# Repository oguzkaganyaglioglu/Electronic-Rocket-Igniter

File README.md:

# Electronic Model Rocket Igniter
## This project still work in progress

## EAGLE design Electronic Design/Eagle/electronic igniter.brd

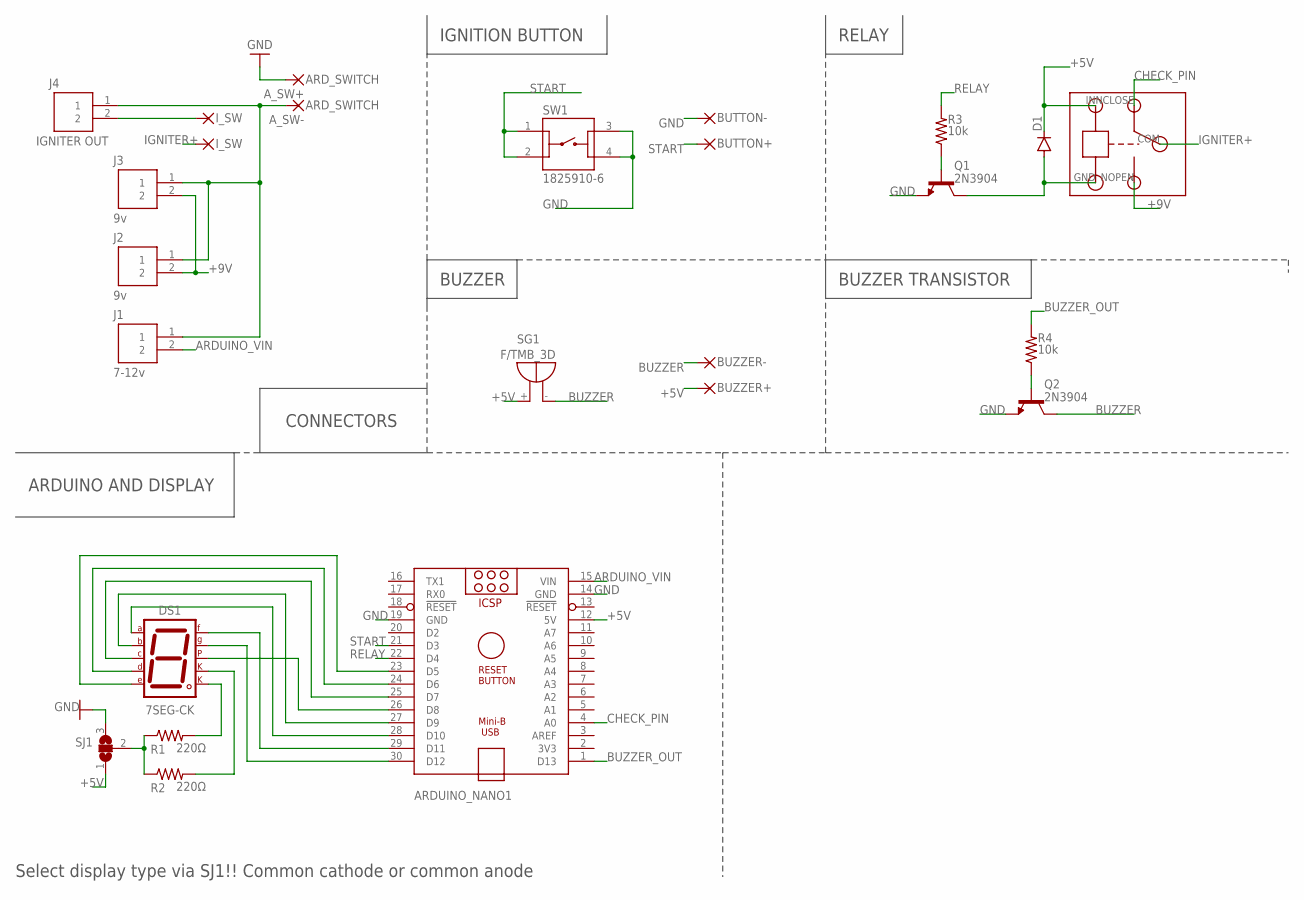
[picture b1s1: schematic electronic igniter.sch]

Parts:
ARDUINO_NANO1: ARDUINO_NANO
A_SW+: ARD_SWITCH; 2,15/1,0
A_SW-: ARD_SWITCH; 2,15/1,0
BUTTON+: 2,15/1,0
BUTTON-: 2,15/1,0
BUZZER+: 2,15/1,0
BUZZER-: 2,15/1,0
D1: 1N4148DO35-7; DO35-7
DS1: 7SEG-CK; 7SEG-13
I_SW+: I_SW; 2,15/1,0
I_SW-: I_SW; 2,15/1,0
J1: 7-12v; 1803277
J2, J3: 9v; 1803277
J4: IGNITER OUT; 1803277
Q1, Q2: 2N3904; TO92
R1, R2: 220Ω; 0204/7
R3, R4: 10k; 0204/7
SG1: F/TMB_3D; F/TMB
SJ1: SJ2WW; SJ_2W
SW1: 1825910-6
U$1: T73; RELAY

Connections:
+5V: ARDUINO_NANO1.12 (5V), BUZZER+.1, D1.C, SG1.+, SJ1.1, U$1.IN
+9V: J2.2, J3.2, U$1.NOPEN
ARDUINO_VIN: ARDUINO_NANO1.15 (VIN), J1.2
BUZZER: BUZZER-.1, Q2.1 (C), SG1.-
BUZZER_OUT: ARDUINO_NANO1.1 (D13), R4.2
CHECK_PIN: ARDUINO_NANO1.4 (A0), U$1.NCLOSE
GND: ARDUINO_NANO1.14 (GND), ARDUINO_NANO1.19 (GND), A_SW+.1, BUTTON-.1, Q1.3 (E), Q2.3 (E), SJ1.3, SW1.3, SW1.4
IGNITER+: I_SW+.1, U$1.COM
IGNITER_OUT: I_SW-.1, J4.2
unnamed: ARDUINO_NANO1.28 (D10), DS1.7 (A)
unnamed: ARDUINO_NANO1.27 (D9), DS1.6 (B)
unnamed: ARDUINO_NANO1.25 (D7), DS1.4 (C)
unnamed: ARDUINO_NANO1.26 (D8), DS1.5 (DP)
unnamed: ARDUINO_NANO1.24 (D6), DS1.2 (D)
unnamed: ARDUINO_NANO1.23 (D5), DS1.1 (E)
unnamed: ARDUINO_NANO1.29 (D11), DS1.9 (F)
unnamed: ARDUINO_NANO1.30 (D12), DS1.10 (G)
unnamed: DS1.3 (CK1), R2.2
unnamed: R1.1, R2.1, SJ1.2
unnamed: DS1.8 (CK2), R1.2
unnamed: D1.A, Q1.1 (C), U$1.GND
unnamed: Q1.2 (B), R3.1
unnamed: A_SW-.1, J1.1, J2.1, J3.1, J4.1
unnamed: Q2.2 (B), R4.1
RELAY: ARDUINO_NANO1.22 (D4), R3.2
START: ARDUINO_NANO1.21 (D3), BUTTON+.1, SW1.1, SW1.2

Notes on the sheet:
CONNECTORS
ARDUINO AND DISPLAY
BUZZER
IGNITION BUTTON
RELAY
BUZZER TRANSISTOR
Select display type via SJ1!! Common cathode or common anode

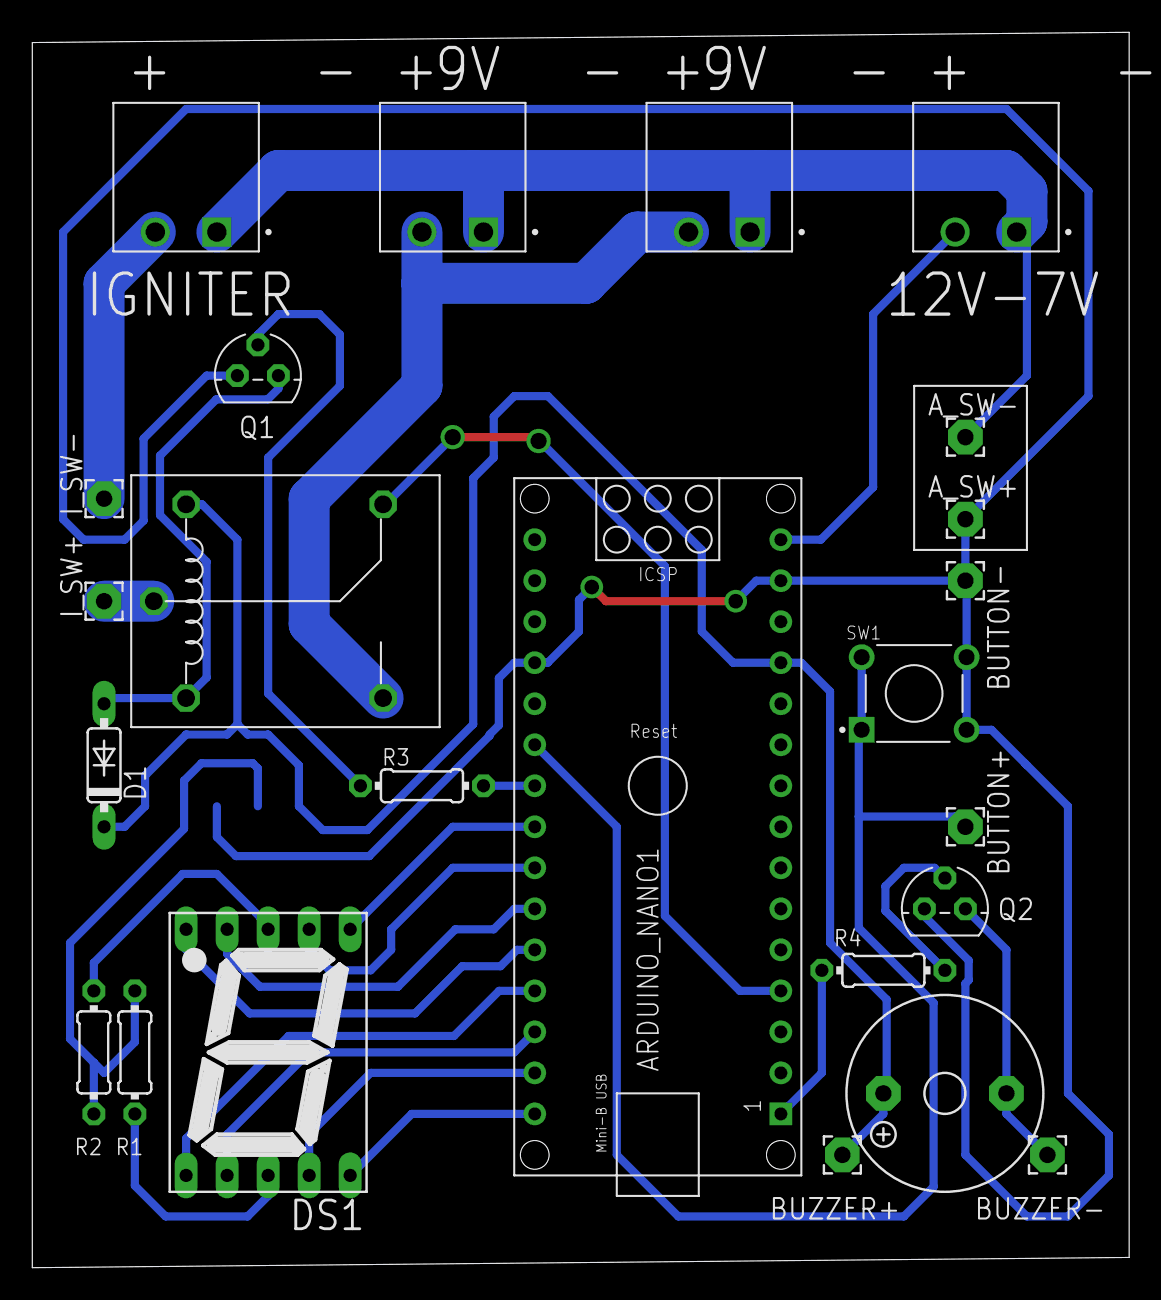
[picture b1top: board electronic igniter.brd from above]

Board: 2 copper layers, 67.9 x 76.5 mm, 25 parts (1 on the bottom side), 26 nets.

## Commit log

2020-11-18 Upload Code
2020-11-19 fix: sound loop
2020-11-20 Electronic Design files added
2020-11-20 readme added
